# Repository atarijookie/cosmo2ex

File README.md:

# Cosmo2ex
This is a continuation / evolution of CosmosEx device. It is an ACSI/SCSI hard drive emulator, floppy emulator, IKBD emulator for Atari 16/32 Bit range of computers

Open design, non-commercial license - see [License](#license).

# What's what

- ce_cores - this is the network server to which the device connects to
- ce_dd_bootsectors	- ACSI/SCSI boot sectors
- ce_dd_prg	- driver for translated/network drives, date setting and screenshots
- android - Android app for switching floppy images from a phone, with a home screen widget
- docker - build and run scripts for ce_cores and webserver running in docker container
- release - builds tarballs + install script for installing directly on a Linux machine (systemd service)
- webserver - a configuration interface via browser

- libacsiscsi - library for access to ACSI/SCSI interface via few functions
- libdospath - long-to-short filename conversion library, emulating DOS paths (8.3)

- test_ce	- Atari test tools, all built into a single app (ce_tests.tos) with a menu to pick the test:
  - test_acsi	- Atari ACSI/SCSI transfer tester
  - test_filesystem	- Atari filesystem tester
  - test_floppy	- Atari floppy emulation tester
  - test_floppy_read	- Atari another floppy emulation tester
  - test_ikbd	- Atari IKBD injection chain tester
  - test_manual, test_manual2	- Atari another ACSI/SCSI transfer testers
  - test_rw, test_rw_user	- Atari ACSI write/read verification testers

# Android floppy app

`android/` is an app for switching floppy images from a phone, with a home screen widget. `android/build.sh` builds it in
docker into `webserver/static/app/`; users get it and connect it on the webserver's Settings → Android app. See `android/README.md`.

# Unit tests

`make test` runs all of them (see the top level `Makefile`, CI runs the same in `.github/workflows/ci.yml`).

- Linux: needs `g++`, `make`, `go` and the `libudev-dev` + `libevdev-dev` packages
- Windows: install [Cygwin](https://www.cygwin.com/) with the `gcc-g++` and `make` packages, then in the Cygwin shell:

      make -C libdospath test
      make -C ce_cores test

  Check out the repository with LF line endings (`git config --global core.autocrlf input` before cloning).
- macOS: needs the Xcode command line tools (`xcode-select --install`), then the same two `make` commands as for Windows

The file tests create their files in `/tmp`. Set `CE_TEST_TMPDIR` to run them on another filesystem, e.g. a
case-insensitive one (like APFS on macOS, FAT or NTFS): `CE_TEST_TMPDIR=/mnt/usb make -C libdospath test`.

# License

Cosmo2ex is open design, non-commercial license: the sources and the hardware designs are public, you can build
it, change it and share it for non-commercial use, but not sell it.

- software and firmware - [PolyForm Noncommercial License 1.0.0](LICENSE)
- hardware designs (schematics, PCBs in `devices/`) - [CC BY-NC-SA 4.0](devices/LICENSE)
- third party code keeps its own license (`third_party/`, and the files that say so in their header)

Building devices for yourself or your friends is fine. Selling devices, kits, PCBs or flashed boards needs a written
commercial license from the author - get in touch first (https://joo.kie.sk).

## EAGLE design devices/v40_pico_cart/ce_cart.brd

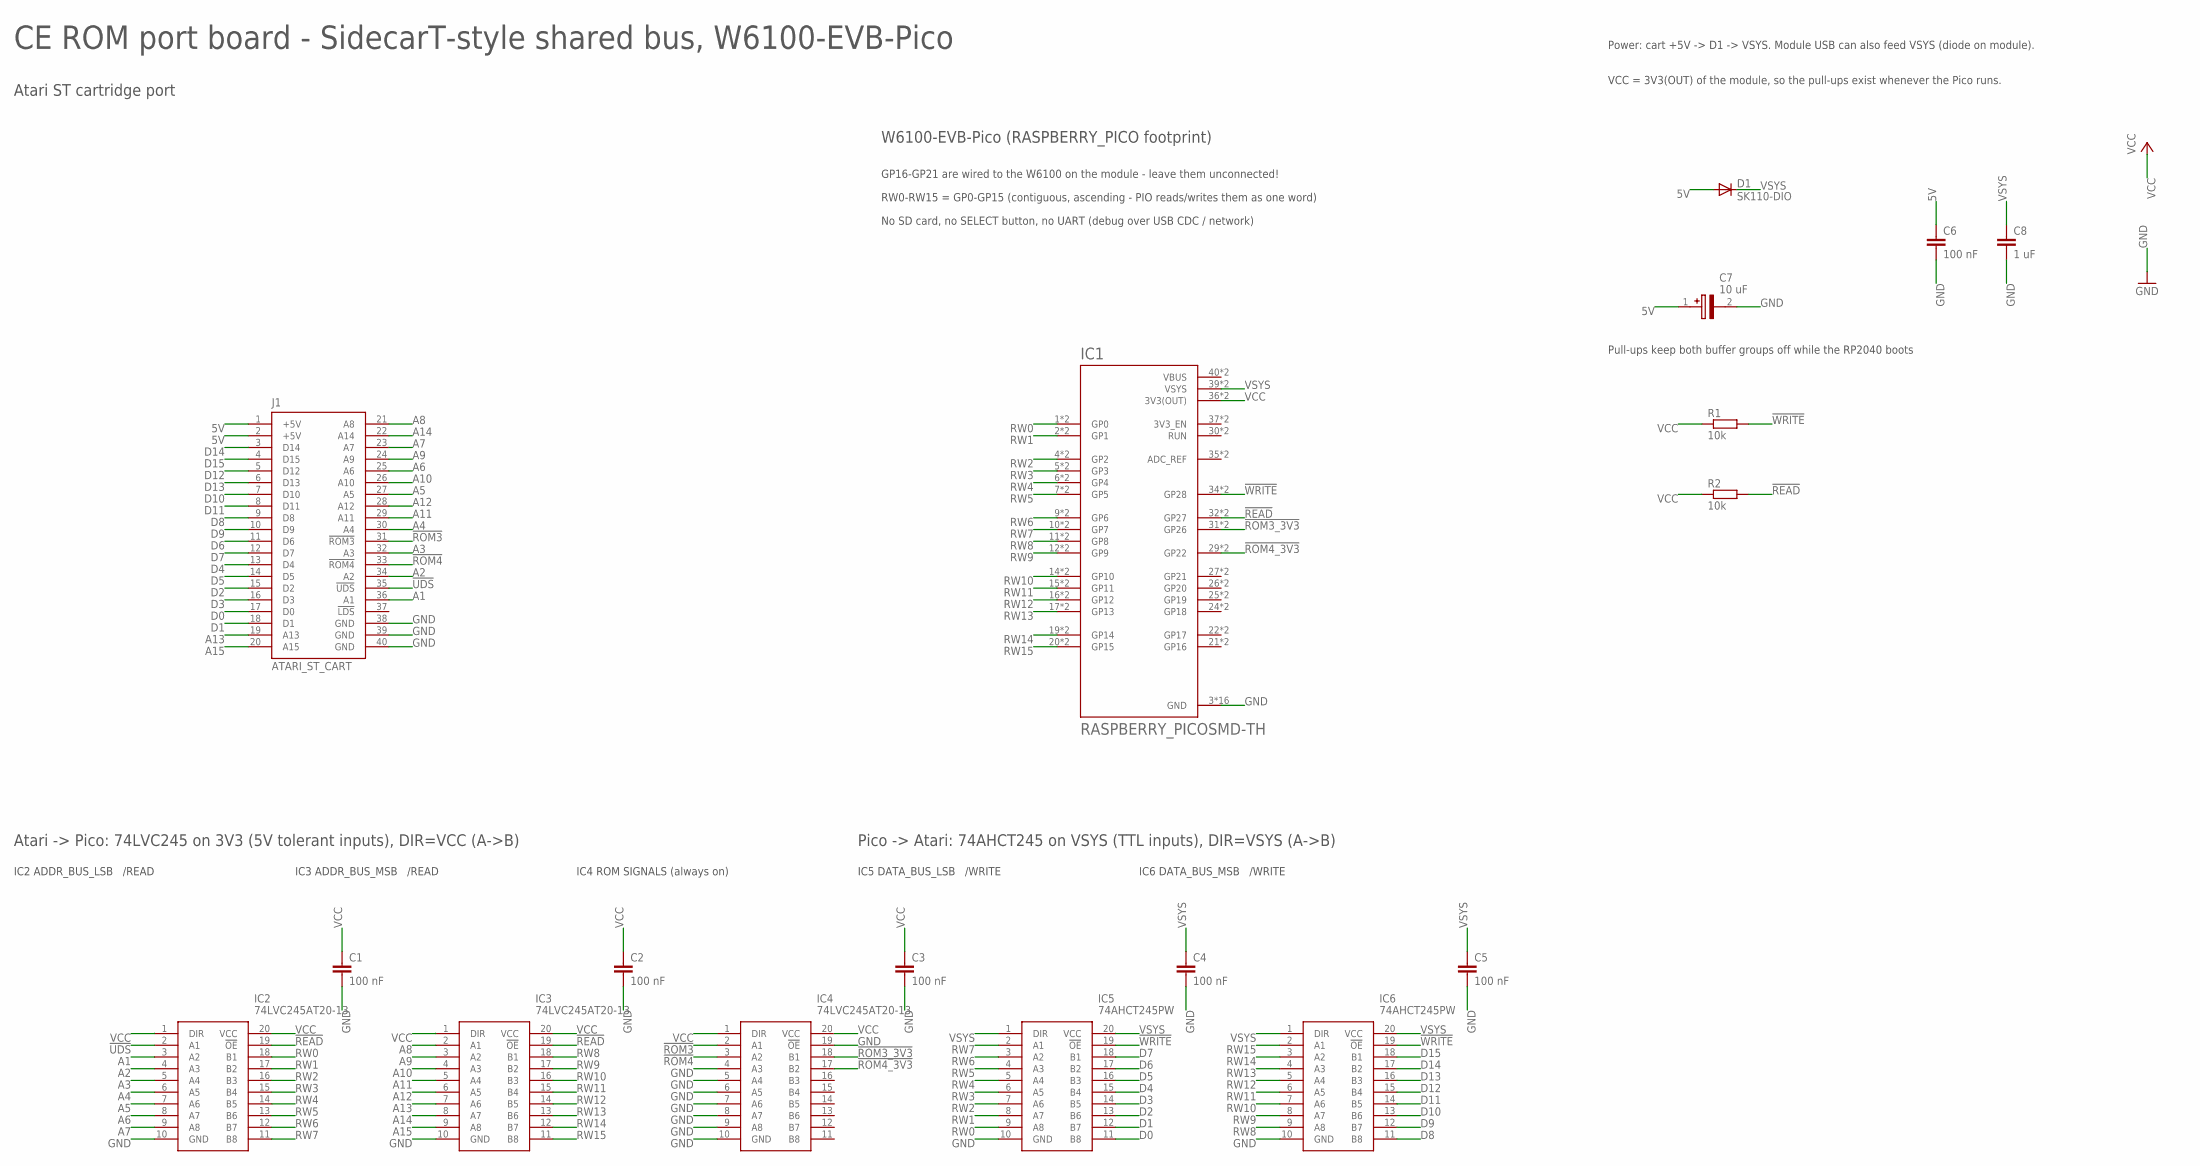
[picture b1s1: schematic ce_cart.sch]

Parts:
C1, C2, C3, C4, C5, C6: 100 nF; C0603
C7: 10 uF; CAPPM3528X210N
C8: 1 uF; C0603
D1: SK110-DIO; DO214AC
IC1: RASPBERRY_PICOSMD-TH; PICO-PKG
IC2, IC3, IC4: 74LVC245AT20-13; SOP65P640X120-20N
IC5, IC6: 74AHCT245PW; SOP65P640X120-20N
J1: ATARI_ST_CART; ST_CART_EDGE_2X20
R1, R2: 10k; R0603

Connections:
5V: C6.1, C7.1 (+), D1.A, J1.1 (+5V), J1.2 (+5V)
!READ: IC1.32 (GP27), IC1.P$32 (GP27), IC2.19 (!OE), IC3.19 (!OE), R2.2
!ROM3: IC4.2 (A1), J1.31 (!ROM3)
!ROM3_3V3: IC1.31 (GP26), IC1.P$31 (GP26), IC4.18 (B1)
!ROM4: IC4.3 (A2), J1.33 (!ROM4)
!ROM4_3V3: IC1.29 (GP22), IC1.P$29 (GP22), IC4.17 (B2)
!UDS: IC2.2 (A1), J1.35 (!UDS)
!WRITE: IC1.34 (GP28), IC1.P$34 (GP28), IC5.19 (!OE), IC6.19 (!OE), R1.2
A1: IC2.3 (A2), J1.36 (A1)
A2: IC2.4 (A3), J1.34 (A2)
A3: IC2.5 (A4), J1.32 (A3)
A4: IC2.6 (A5), J1.30 (A4)
A5: IC2.7 (A6), J1.27 (A5)
A6: IC2.8 (A7), J1.25 (A6)
A7: IC2.9 (A8), J1.23 (A7)
A8: IC3.2 (A1), J1.21 (A8)
A9: IC3.3 (A2), J1.24 (A9)
A10: IC3.4 (A3), J1.26 (A10)
A11: IC3.5 (A4), J1.29 (A11)
A12: IC3.6 (A5), J1.28 (A12)
A13: IC3.7 (A6), J1.19 (A13)
A14: IC3.8 (A7), J1.22 (A14)
A15: IC3.9 (A8), J1.20 (A15)
D0: IC5.11 (B8), J1.17 (D0)
D1: IC5.12 (B7), J1.18 (D1)
D2: IC5.13 (B6), J1.15 (D2)
D3: IC5.14 (B5), J1.16 (D3)
D4: IC5.15 (B4), J1.13 (D4)
D5: IC5.16 (B3), J1.14 (D5)
D6: IC5.17 (B2), J1.11 (D6)
D7: IC5.18 (B1), J1.12 (D7)
D8: IC6.11 (B8), J1.9 (D8)
D9: IC6.12 (B7), J1.10 (D9)
D10: IC6.13 (B6), J1.7 (D10)
D11: IC6.14 (B5), J1.8 (D11)
D12: IC6.15 (B4), J1.5 (D12)
D13: IC6.16 (B3), J1.6 (D13)
D14: IC6.17 (B2), J1.3 (D14)
D15: IC6.18 (B1), J1.4 (D15)
GND: C1.2, C2.2, C3.2, C4.2, C5.2, C6.2, C7.2 (-), C8.2, IC1.3 (GND), IC1.8 (GND), IC1.13 (GND), IC1.18 (GND), IC1.23 (GND), IC1.28 (GND), IC1.33 (GND), IC1.38 (GND), IC1.P$3 (GND), IC1.P$8 (GND), IC1.P$13 (GND), IC1.P$18 (GND), IC1.P$23 (GND), IC1.P$28 (GND), IC1.P$33 (GND), IC1.P$38 (GND), IC2.10 (GND), IC3.10 (GND), IC4.4 (A3), IC4.5 (A4), IC4.6 (A5), IC4.7 (A6), IC4.8 (A7), IC4.9 (A8), IC4.10 (GND), IC4.19 (!OE), IC5.10 (GND), IC6.10 (GND), J1.38 (GND), J1.39 (GND), J1.40 (GND)
RW0: IC1.1 (GP0), IC1.P$1 (GP0), IC2.18 (B1), IC5.9 (A8)
RW1: IC1.2 (GP1), IC1.P$2 (GP1), IC2.17 (B2), IC5.8 (A7)
RW2: IC1.4 (GP2), IC1.P$4 (GP2), IC2.16 (B3), IC5.7 (A6)
RW3: IC1.5 (GP3), IC1.P$5 (GP3), IC2.15 (B4), IC5.6 (A5)
RW4: IC1.6 (GP4), IC1.P$6 (GP4), IC2.14 (B5), IC5.5 (A4)
RW5: IC1.7 (GP5), IC1.P$7 (GP5), IC2.13 (B6), IC5.4 (A3)
RW6: IC1.9 (GP6), IC1.P$9 (GP6), IC2.12 (B7), IC5.3 (A2)
RW7: IC1.10 (GP7), IC1.P$10 (GP7), IC2.11 (B8), IC5.2 (A1)
RW8: IC1.11 (GP8), IC1.P$11 (GP8), IC3.18 (B1), IC6.9 (A8)
RW9: IC1.12 (GP9), IC1.P$12 (GP9), IC3.17 (B2), IC6.8 (A7)
RW10: IC1.14 (GP10), IC1.P$14 (GP10), IC3.16 (B3), IC6.7 (A6)
RW11: IC1.15 (GP11), IC1.P$15 (GP11), IC3.15 (B4), IC6.6 (A5)
RW12: IC1.16 (GP12), IC1.P$16 (GP12), IC3.14 (B5), IC6.5 (A4)
RW13: IC1.17 (GP13), IC1.P$17 (GP13), IC3.13 (B6), IC6.4 (A3)
RW14: IC1.19 (GP14), IC1.P$19 (GP14), IC3.12 (B7), IC6.3 (A2)
RW15: IC1.20 (GP15), IC1.P$20 (GP15), IC3.11 (B8), IC6.2 (A1)
VBUS: IC1.40 (VBUS), IC1.P$40 (VBUS)
VCC: C1.1, C2.1, C3.1, IC1.36 (3V3(OUT)), IC1.P$36 (3V3(OUT)), IC2.1 (DIR), IC2.20 (VCC), IC3.1 (DIR), IC3.20 (VCC), IC4.1 (DIR), IC4.20 (VCC), R1.1, R2.1
VSYS: C4.1, C5.1, C8.1, D1.C, IC1.39 (VSYS), IC1.P$39 (VSYS), IC5.1 (DIR), IC5.20 (VCC), IC6.1 (DIR), IC6.20 (VCC)

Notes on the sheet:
CE ROM port board - SidecarT-style shared bus, W6100-EVB-Pico
Atari ST cartridge port
W6100-EVB-Pico (RASPBERRY_PICO footprint)
GP16-GP21 are wired to the W6100 on the module - leave them unconnected!
RW0-RW15 = GP0-GP15 (contiguous, ascending - PIO reads/writes them as one word)
No SD card, no SELECT button, no UART (debug over USB CDC / network)
Power: cart +5V -> D1 -> VSYS. Module USB can also feed VSYS (diode on module).
VCC = 3V3(OUT) of the module, so the pull-ups exist whenever the Pico runs.
Pull-ups keep both buffer groups off while the RP2040 boots
Atari -> Pico: 74LVC245 on 3V3 (5V tolerant inputs), DIR=VCC (A->B)
IC2 ADDR_BUS_LSB /READ
IC3 ADDR_BUS_MSB /READ
IC4 ROM SIGNALS (always on)
Pico -> Atari: 74AHCT245 on VSYS (TTL inputs), DIR=VSYS (A->B)
IC5 DATA_BUS_LSB /WRITE
IC6 DATA_BUS_MSB /WRITE

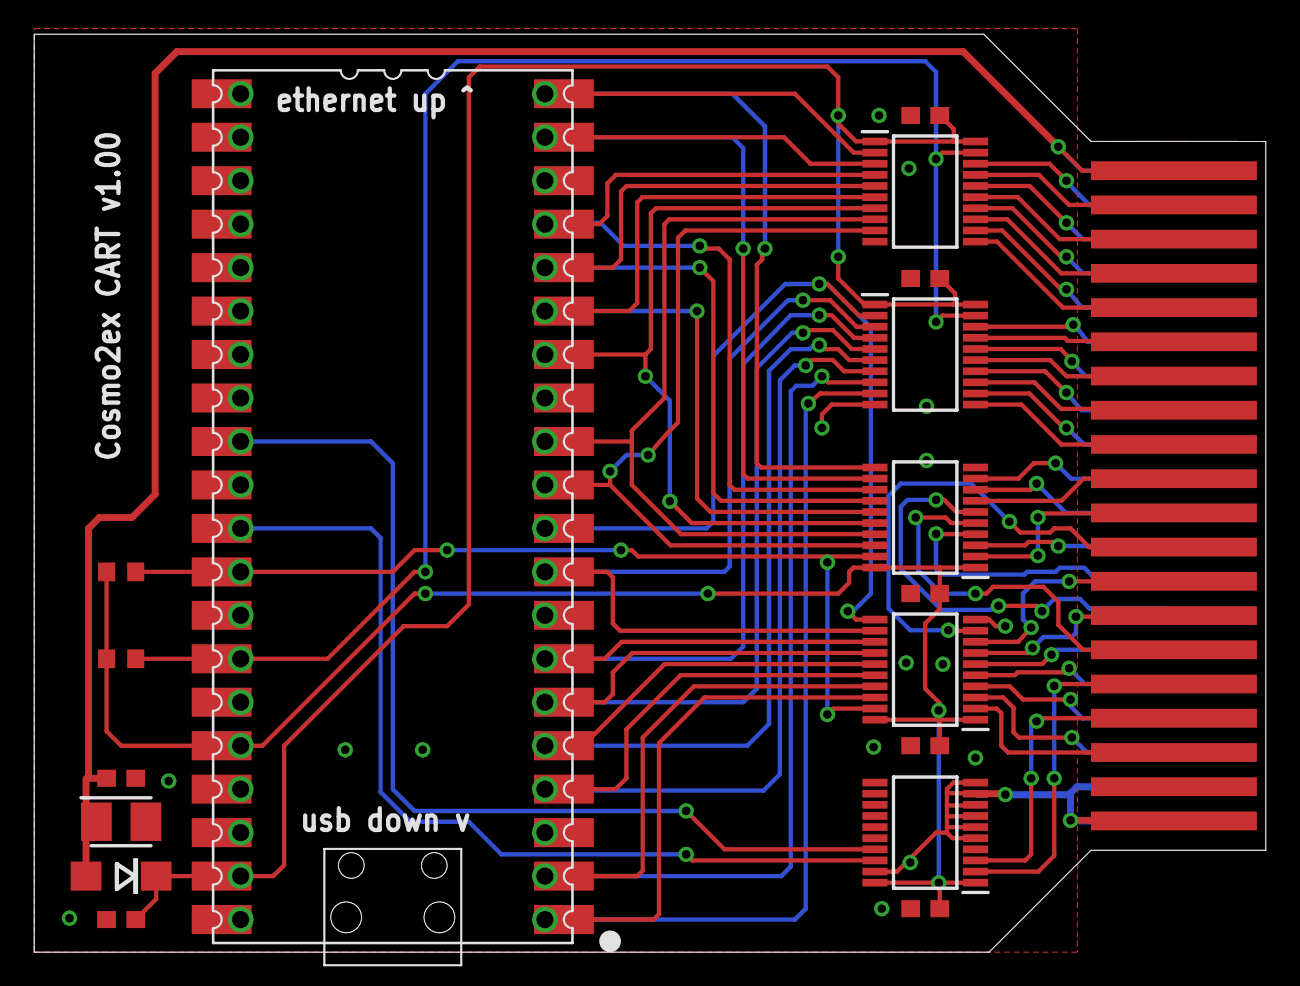
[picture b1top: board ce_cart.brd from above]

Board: 2 copper layers, 72.0 x 53.6 mm, 18 parts (0 on the bottom side), 59 nets.

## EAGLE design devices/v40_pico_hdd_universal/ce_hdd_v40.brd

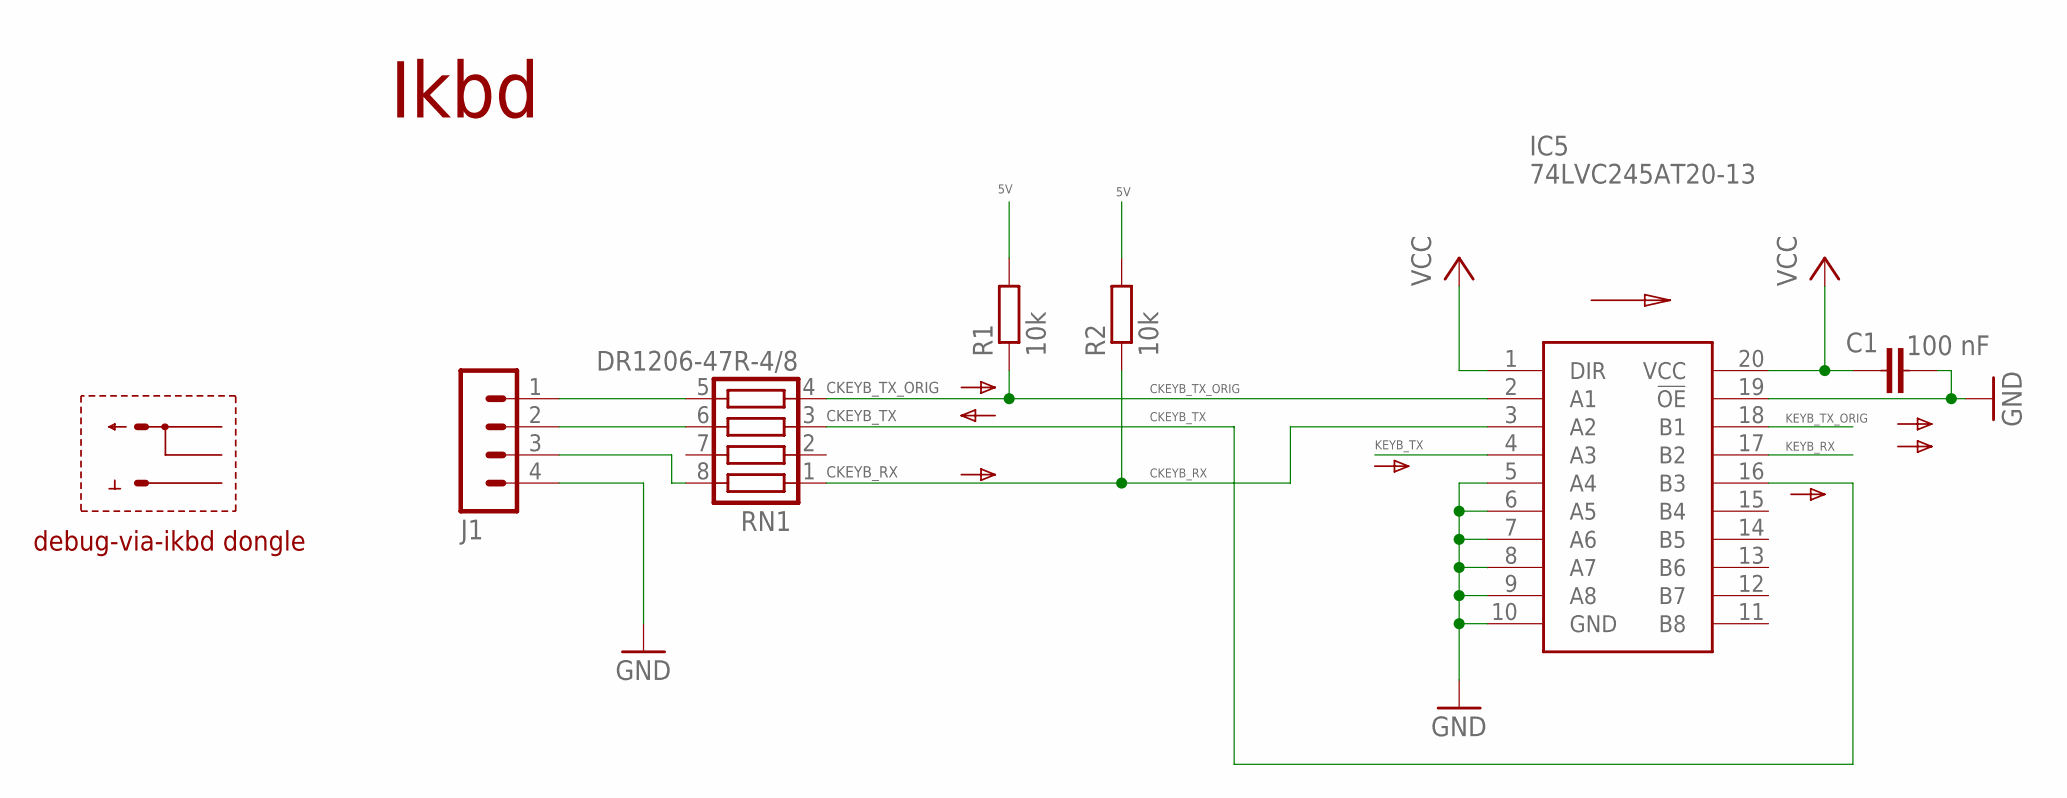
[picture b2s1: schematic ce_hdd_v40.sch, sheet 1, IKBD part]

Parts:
C1: 100 nF; C0603
IC5: 74LVC245AT20-13; SOP65P640X120-20N
J1: MA04-1
R1, R2: 10k; R0603
RN1: DR1206-47R-4/8; CTS742C083

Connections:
5V: R1.2, R2.2; also elsewhere on the board
CKEYB_RX: IC5.3 (A2), R2.1, RN1.1
CKEYB_TX: IC5.16 (B3), RN1.3
CKEYB_TX_ORIG: IC5.2 (A1), R1.1, RN1.4
GND: C1.1, IC5.5 (A4), IC5.6 (A5), IC5.7 (A6), IC5.8 (A7), IC5.9 (A8), IC5.10 (GND), IC5.19 (!OE), J1.4; also elsewhere on the board
KEYB_RX: IC5.17 (B2); also elsewhere on the board
KEYB_TX: IC5.4 (A3); also elsewhere on the board
KEYB_TX_ORIG: IC5.18 (B1); also elsewhere on the board
unnamed: J1.2, RN1.6
VCC: C1.2, IC5.1 (DIR), IC5.20 (VCC); also elsewhere on the board
ZKEYB_RX: J1.3, RN1.8
ZKEYB_TX_ORIG: J1.1, RN1.5

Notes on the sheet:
Ikbd
debug-via-ikbd dongle

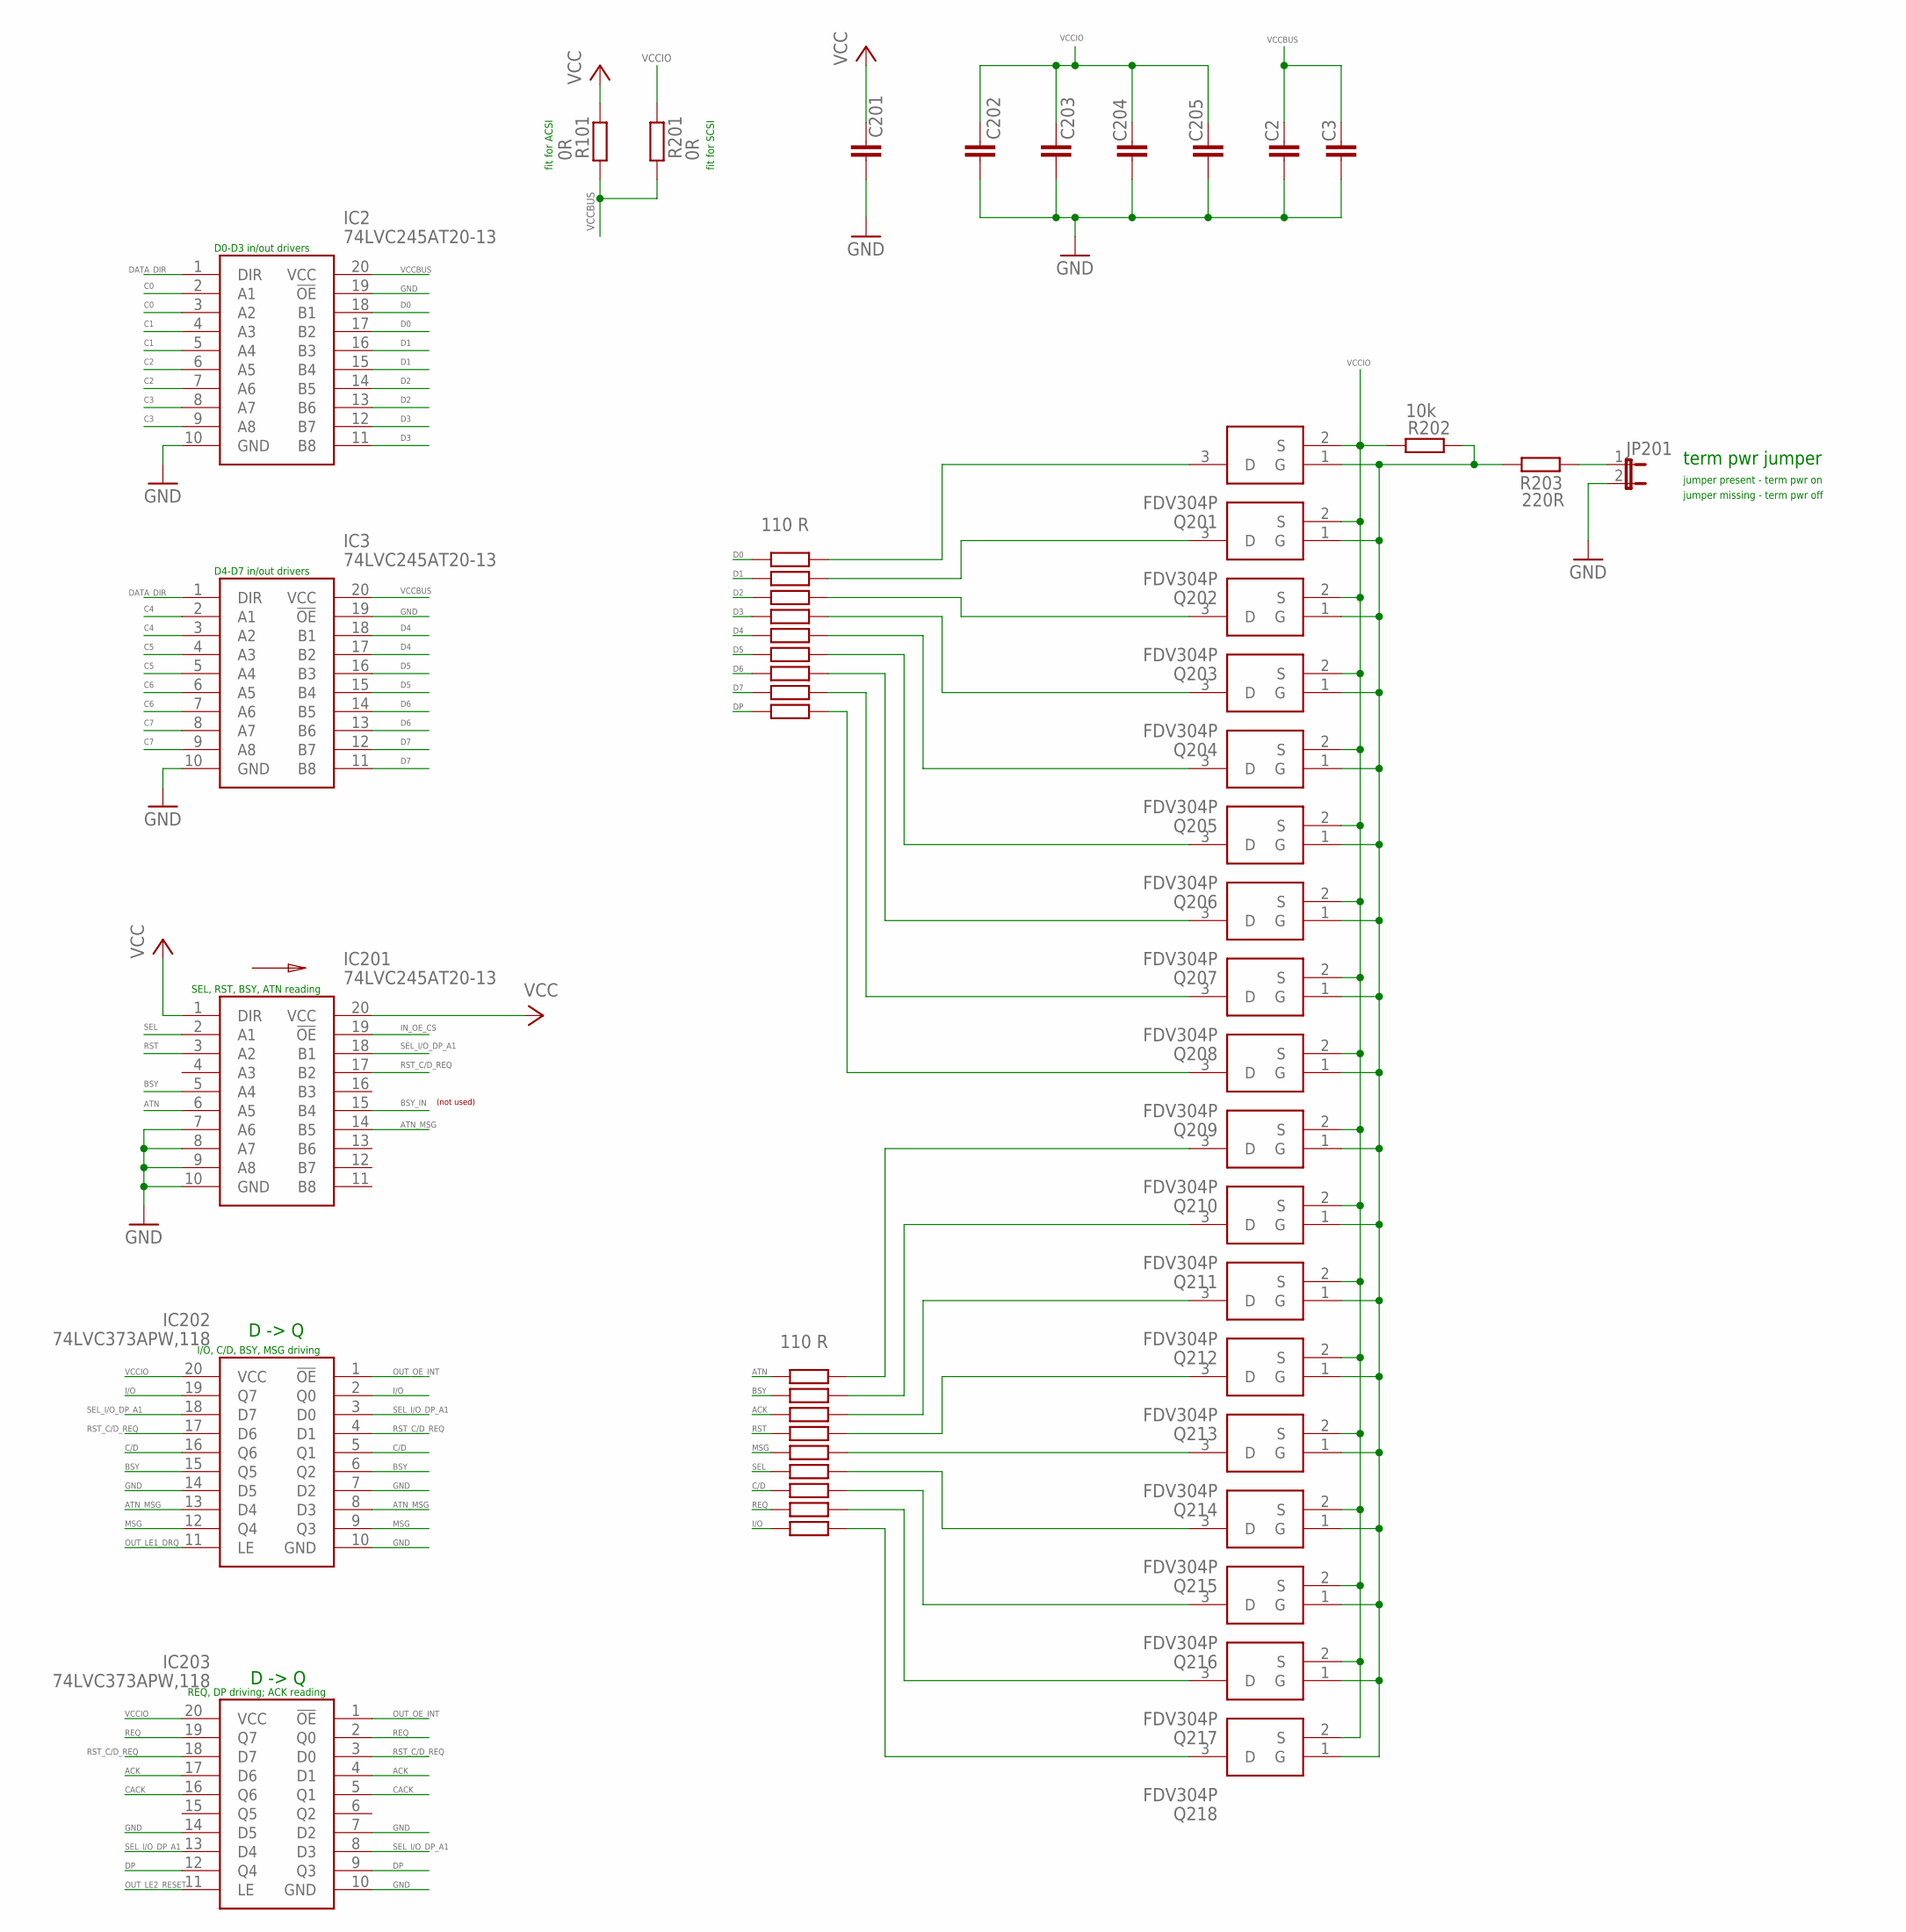
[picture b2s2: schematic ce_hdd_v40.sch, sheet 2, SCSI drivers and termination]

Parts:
C2, C3, C201, C202, C204, C205: 100 nF; C0603
C203: 1 uF; C0603
IC2, IC3, IC201: 74LVC245AT20-13; SOP65P640X120-20N
IC202, IC203: 74LVC373APW,118; SOP65P640X110-20N
JP201: JP1E; JP1
Q201, Q202, Q203, Q204, Q205, Q206, Q207, Q208, Q209, Q210, Q211, Q212, Q213, Q214, Q215, Q216, Q217, Q218: FDV304P; SOT95P237X112-3N
R101, R201: 0R; R0603
R202: 10k; R0603
R203: 220R; R0603
R204, R205, R206, R207, R208, R209, R210, R211, R212, R213, R214, R215, R216, R217, R218, R219, R220, R221: 110 R; R0603

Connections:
AAAA: Q201.3 (D), R204.1
ACK: IC203.4 (D1), IC203.17 (D6), R215.2; also elsewhere on the board
ATN: IC201.6 (A5), R213.2; also elsewhere on the board
ATN_MSG: IC201.14 (B5), IC202.8 (D3), IC202.13 (D4); also elsewhere on the board
BSY: IC201.5 (A4), IC202.6 (Q2), IC202.15 (Q5), R214.2; also elsewhere on the board
BSY_IN: IC201.15 (B4)
C0: IC2.2 (A1), IC2.3 (A2); also elsewhere on the board
C1: IC2.4 (A3), IC2.5 (A4); also elsewhere on the board
C2: IC2.6 (A5), IC2.7 (A6); also elsewhere on the board
C3: IC2.8 (A7), IC2.9 (A8); also elsewhere on the board
C4: IC3.2 (A1), IC3.3 (A2); also elsewhere on the board
C5: IC3.4 (A3), IC3.5 (A4); also elsewhere on the board
C6: IC3.6 (A5), IC3.7 (A6); also elsewhere on the board
C7: IC3.8 (A7), IC3.9 (A8); also elsewhere on the board
C/D: IC202.5 (Q1), IC202.16 (Q6), R219.2; also elsewhere on the board
CACK: IC203.5 (Q1), IC203.16 (Q6); also elsewhere on the board
D0: IC2.17 (B2), IC2.18 (B1), R204.2; also elsewhere on the board
D1: IC2.15 (B4), IC2.16 (B3), R205.2; also elsewhere on the board
D2: IC2.13 (B6), IC2.14 (B5), R206.2; also elsewhere on the board
D3: IC2.11 (B8), IC2.12 (B7), R207.2; also elsewhere on the board
D4: IC3.17 (B2), IC3.18 (B1), R208.2; also elsewhere on the board
D5: IC3.15 (B4), IC3.16 (B3), R209.2; also elsewhere on the board
D6: IC3.13 (B6), IC3.14 (B5), R210.2; also elsewhere on the board
D7: IC3.11 (B8), IC3.12 (B7), R211.2; also elsewhere on the board
DATA_DIR: IC2.1 (DIR), IC3.1 (DIR); also elsewhere on the board
DP: IC203.9 (Q3), IC203.12 (Q4), R212.2; also elsewhere on the board
GND: C2.2, C3.2, C201.2, C202.2, C203.2, C204.2, C205.2, IC2.10 (GND), IC2.19 (!OE), IC3.10 (GND), IC3.19 (!OE), IC201.7 (A6), IC201.8 (A7), IC201.9 (A8), IC201.10 (GND), IC202.7 (D2), IC202.10 (GND), IC202.14 (D5), IC203.7 (D2), IC203.10 (GND), IC203.14 (D5), JP201.2; also elsewhere on the board
I/O: IC202.2 (Q0), IC202.19 (Q7), R221.2; also elsewhere on the board
IN_OE_CS: IC201.19 (!OE); also elsewhere on the board
MSG: IC202.9 (Q3), IC202.12 (Q4), R217.2; also elsewhere on the board
unnamed: JP201.1, R203.2
unnamed: Q202.3 (D), R205.1
unnamed: Q203.3 (D), R206.1
unnamed: Q204.3 (D), R207.1
unnamed: Q205.3 (D), R208.1
unnamed: Q206.3 (D), R209.1
unnamed: Q207.3 (D), R210.1
unnamed: Q208.3 (D), R211.1
unnamed: Q209.3 (D), R212.1
unnamed: Q210.3 (D), R213.1
unnamed: Q211.3 (D), R214.1
unnamed: Q212.3 (D), R215.1
unnamed: Q213.3 (D), R216.1
unnamed: Q214.3 (D), R217.1
unnamed: Q215.3 (D), R218.1
unnamed: Q216.3 (D), R219.1
unnamed: Q217.3 (D), R220.1
unnamed: Q218.3 (D), R221.1
OUT_LE1_DRQ: IC202.11 (LE); also elsewhere on the board
OUT_LE2_RESET: IC203.11 (LE); also elsewhere on the board
OUT_OE_INT: IC202.1 (!OE), IC203.1 (!OE); also elsewhere on the board
REQ: IC203.2 (Q0), IC203.19 (Q7), R220.2; also elsewhere on the board
RST: IC201.3 (A2), R216.2; also elsewhere on the board
RST_C/D_REQ: IC201.17 (B2), IC202.4 (D1), IC202.17 (D6), IC203.3 (D0), IC203.18 (D7); also elsewhere on the board
SEL: IC201.2 (A1), R218.2; also elsewhere on the board
SEL_I/O_DP_A1: IC201.18 (B1), IC202.3 (D0), IC202.18 (D7), IC203.8 (D3), IC203.13 (D4); also elsewhere on the board
TP_ON: Q201.1 (G), Q202.1 (G), Q203.1 (G), Q204.1 (G), Q205.1 (G), Q206.1 (G), Q207.1 (G), Q208.1 (G), Q209.1 (G), Q210.1 (G), Q211.1 (G), Q212.1 (G), Q213.1 (G), Q214.1 (G), Q215.1 (G), Q216.1 (G), Q217.1 (G), Q218.1 (G), R202.2, R203.1
VCC: C201.1, IC201.1 (DIR), IC201.20 (VCC), R101.2; also elsewhere on the board
VCCBUS: C2.1, C3.1, IC2.20 (VCC), IC3.20 (VCC), R101.1, R201.1
VCCIO: C202.1, C203.1, C204.1, C205.1, IC202.20 (VCC), IC203.20 (VCC), Q201.2 (S), Q202.2 (S), Q203.2 (S), Q204.2 (S), Q205.2 (S), Q206.2 (S), Q207.2 (S), Q208.2 (S), Q209.2 (S), Q210.2 (S), Q211.2 (S), Q212.2 (S), Q213.2 (S), Q214.2 (S), Q215.2 (S), Q216.2 (S), Q217.2 (S), Q218.2 (S), R201.2, R202.1; also elsewhere on the board

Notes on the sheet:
D -> Q
term pwr jumper
jumper present - term pwr on
jumper missing - term pwr off
D0-D3 in/out drivers
D4-D7 in/out drivers
SEL, RST, BSY, ATN reading
I/O, C/D, BSY, MSG driving
REQ, DP driving; ACK reading
(not used)
fit for ACSI
fit for SCSI

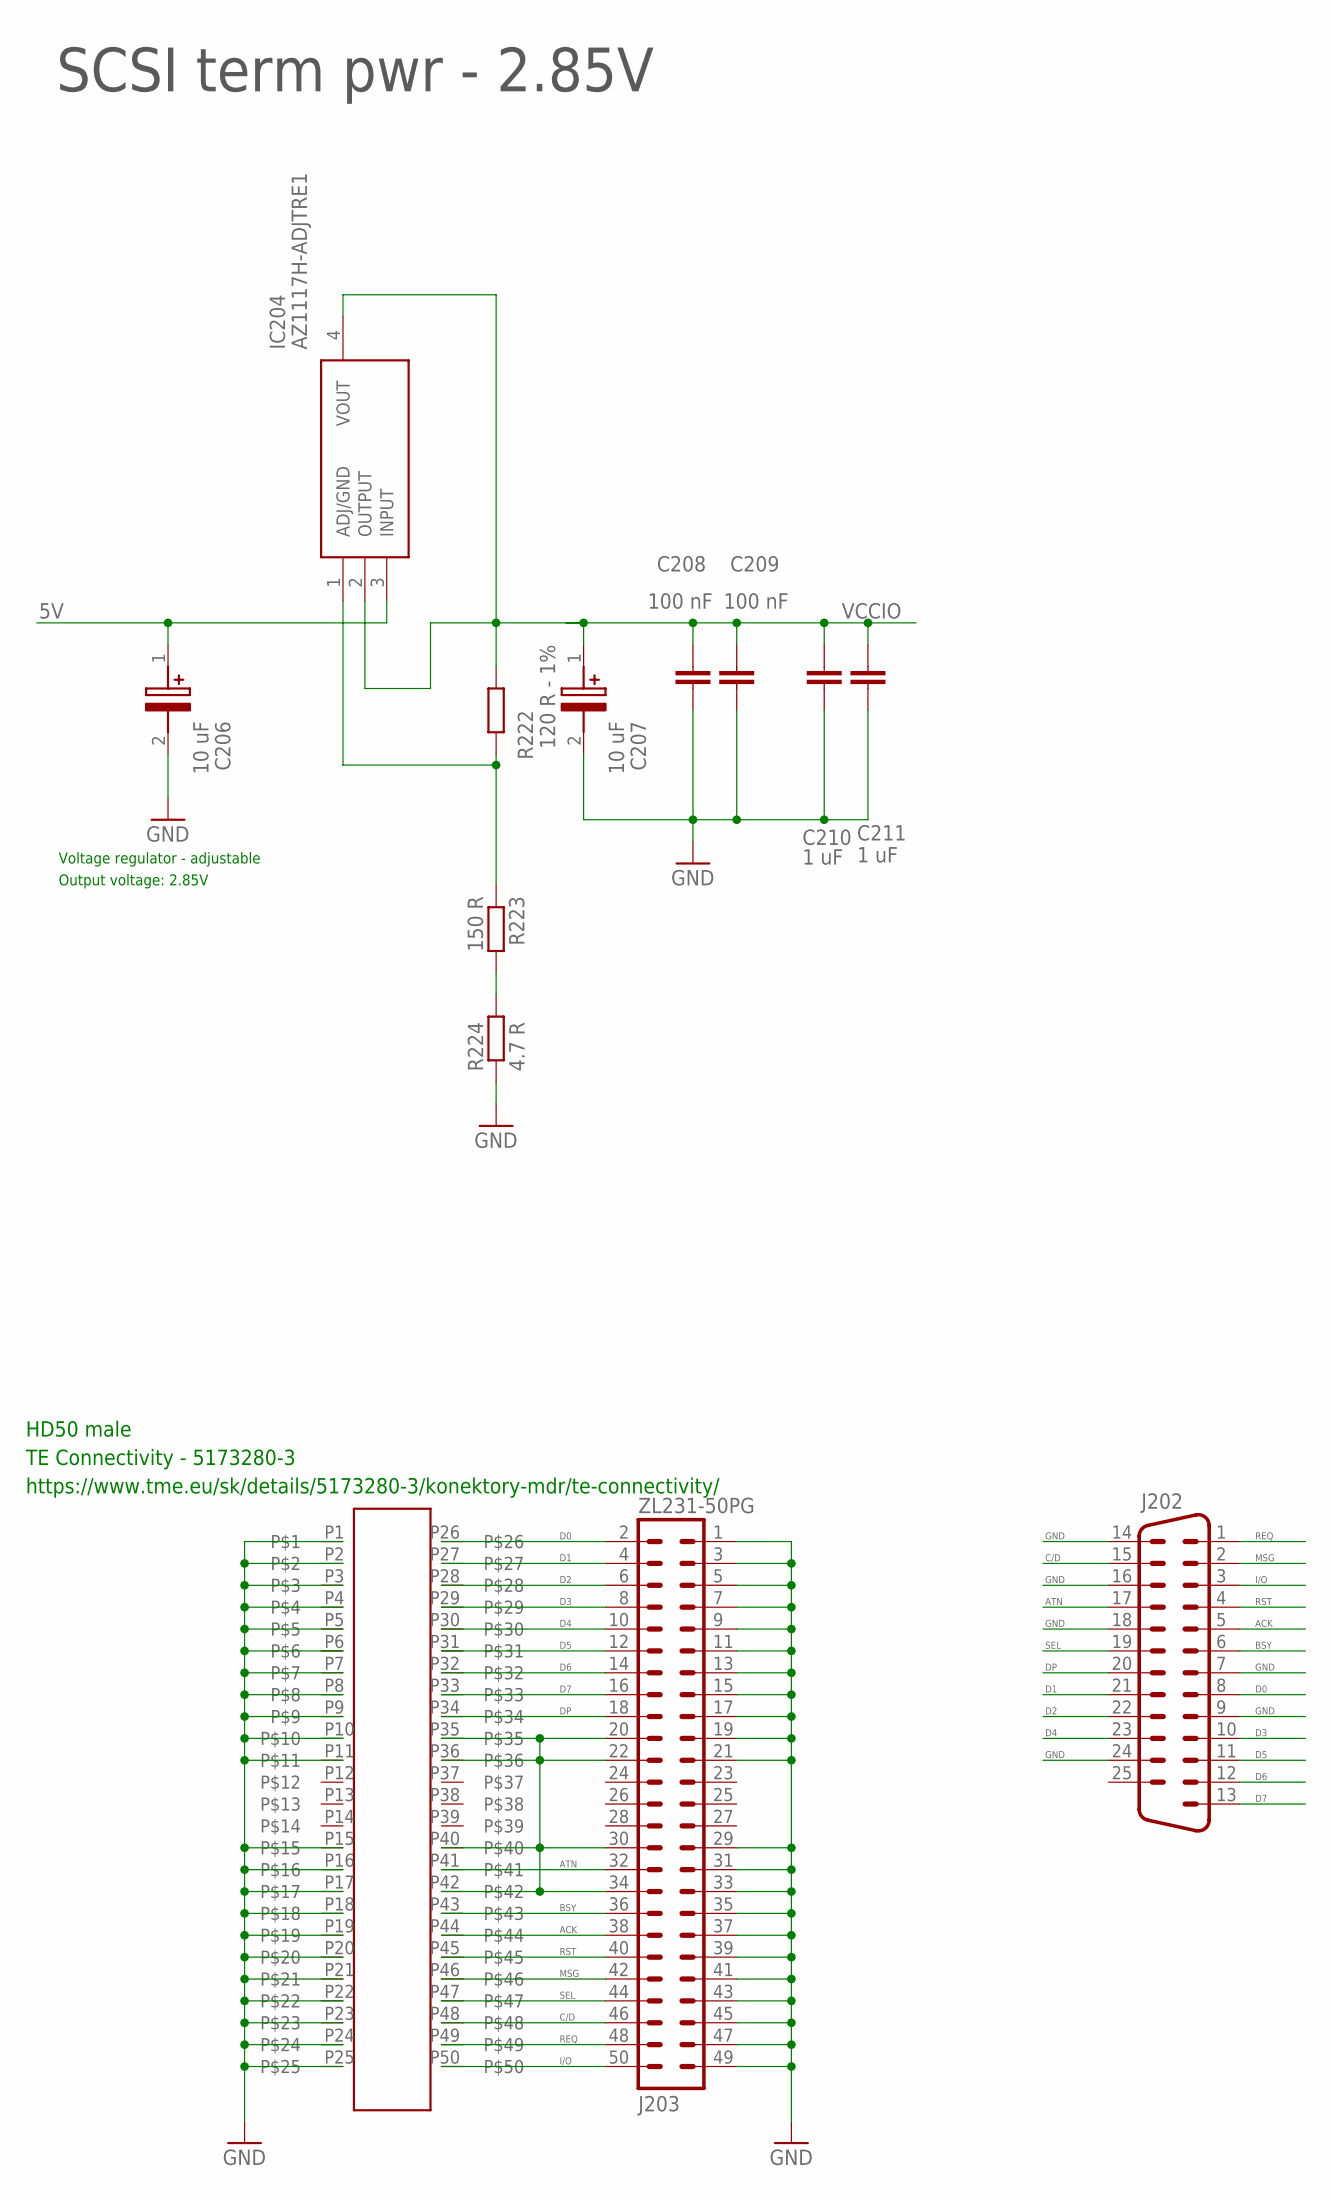
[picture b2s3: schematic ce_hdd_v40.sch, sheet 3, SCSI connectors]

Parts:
C206, C207: 10 uF; CAPPM3528X210N; MANUFACTURER_PART_NUMBER 293D106X9016B2TE3
C208, C209: 100 nF; C0603
C210, C211: 1 uF; C0603
IC204: AZ1117H-ADJTRE1; SOT230P700X185-4N
J201: TE Connectivity - 5173280-3; HD50_MALE
J202: M25V
J203: ZL231-50PG; ML50
R222: 120 R - 1%; R0603
R223: 150 R; R0603
R224: 4.7 R; R0603

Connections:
5V: C206.1 (+), IC204.3 (INPUT); also elsewhere on the board
ACK: J201.P44, J202.5, J203.38; also elsewhere on the board
ATN: J201.P41, J202.17, J203.32; also elsewhere on the board
BSY: J201.P43, J202.6, J203.36; also elsewhere on the board
C/D: J201.P48, J202.15, J203.46; also elsewhere on the board
D0: J201.P26, J202.8, J203.2; also elsewhere on the board
D1: J201.P27, J202.21, J203.4; also elsewhere on the board
D2: J201.P28, J202.22, J203.6; also elsewhere on the board
D3: J201.P29, J202.10, J203.8; also elsewhere on the board
D4: J201.P30, J202.23, J203.10; also elsewhere on the board
D5: J201.P31, J202.11, J203.12; also elsewhere on the board
D6: J201.P32, J202.12, J203.14; also elsewhere on the board
D7: J201.P33, J202.13, J203.16; also elsewhere on the board
DP: J201.P34, J202.20, J203.18; also elsewhere on the board
GND: C206.2 (-), C207.2 (-), C208.2, C209.2, C210.2, C211.2, J201.P1, J201.P2, J201.P3, J201.P4, J201.P5, J201.P6, J201.P7, J201.P8, J201.P9, J201.P10, J201.P11, J201.P15, J201.P16, J201.P17, J201.P18, J201.P19, J201.P20, J201.P21, J201.P22, J201.P23, J201.P24, J201.P25, J201.P35, J201.P36, J201.P40, J201.P42, J202.7, J202.9, J202.14, J202.16, J202.18, J202.24, J203.1, J203.3, J203.5, J203.7, J203.9, J203.11, J203.13, J203.15, J203.17, J203.19, J203.20, J203.21, J203.22, J203.29, J203.30, J203.31, J203.33, J203.34, J203.35, J203.37, J203.39, J203.41, J203.43, J203.45, J203.47, J203.49, R224.1; also elsewhere on the board
I/O: J201.P50, J202.3, J203.50; also elsewhere on the board
MSG: J201.P46, J202.2, J203.42; also elsewhere on the board
unnamed: R223.2, R224.2
unnamed: IC204.1 (ADJ/GND), R222.2, R223.1
REQ: J201.P49, J202.1, J203.48; also elsewhere on the board
RST: J201.P45, J202.4, J203.40; also elsewhere on the board
SEL: J201.P47, J202.19, J203.44; also elsewhere on the board
VCCIO: C207.1 (+), C208.1, C209.1, C210.1, C211.1, IC204.2 (OUTPUT), IC204.4 (VOUT), R222.1; also elsewhere on the board

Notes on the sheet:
Voltage regulator - adjustable
Output voltage: 2.85V
SCSI term pwr - 2.85V
HD50 male
TE Connectivity - 5173280-3
https://www.tme.eu/sk/details/5173280-3/konektory-mdr/te-connectivity/
